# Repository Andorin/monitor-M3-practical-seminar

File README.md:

monitor-M3-practical-seminar
============================

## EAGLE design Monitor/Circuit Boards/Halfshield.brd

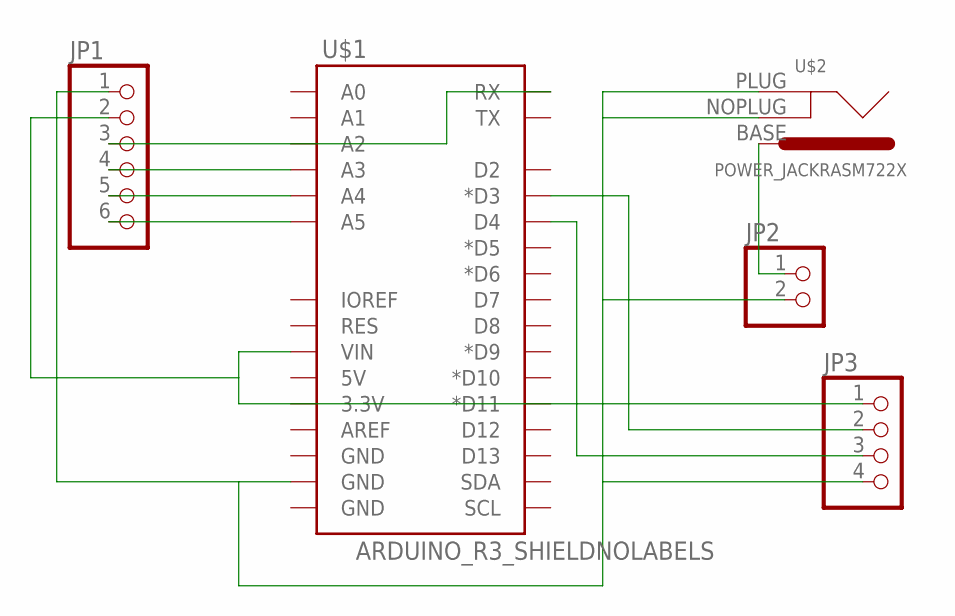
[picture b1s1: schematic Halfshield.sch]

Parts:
JP1: PINHD-1X6; 1X06
JP2: PINHD-1X2; 1X02
JP3: PINHD-1X4; 1X04
U$1: ARDUINO_R3_SHIELDNOLABELS; UNO_R3_SHIELD_NOLABELS
U$2: POWER_JACKRASM722X; RASM722X

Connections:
unnamed: JP1.6, U$1.A5
unnamed: JP1.5, U$1.A4
unnamed: JP1.4, U$1.A3
unnamed: JP1.3, U$1.RX
unnamed: JP1.2, JP3.1, U$1.VIN
unnamed: JP2.1, U$2.BASE (GND)
unnamed: JP1.1, JP2.2, JP3.4, U$1.GND@1 (GND), U$2.NOPLUG (OFF), U$2.PLUG (ON)
unnamed: JP3.3, U$1.D4
unnamed: JP3.2, U$1.D3 (*D3)

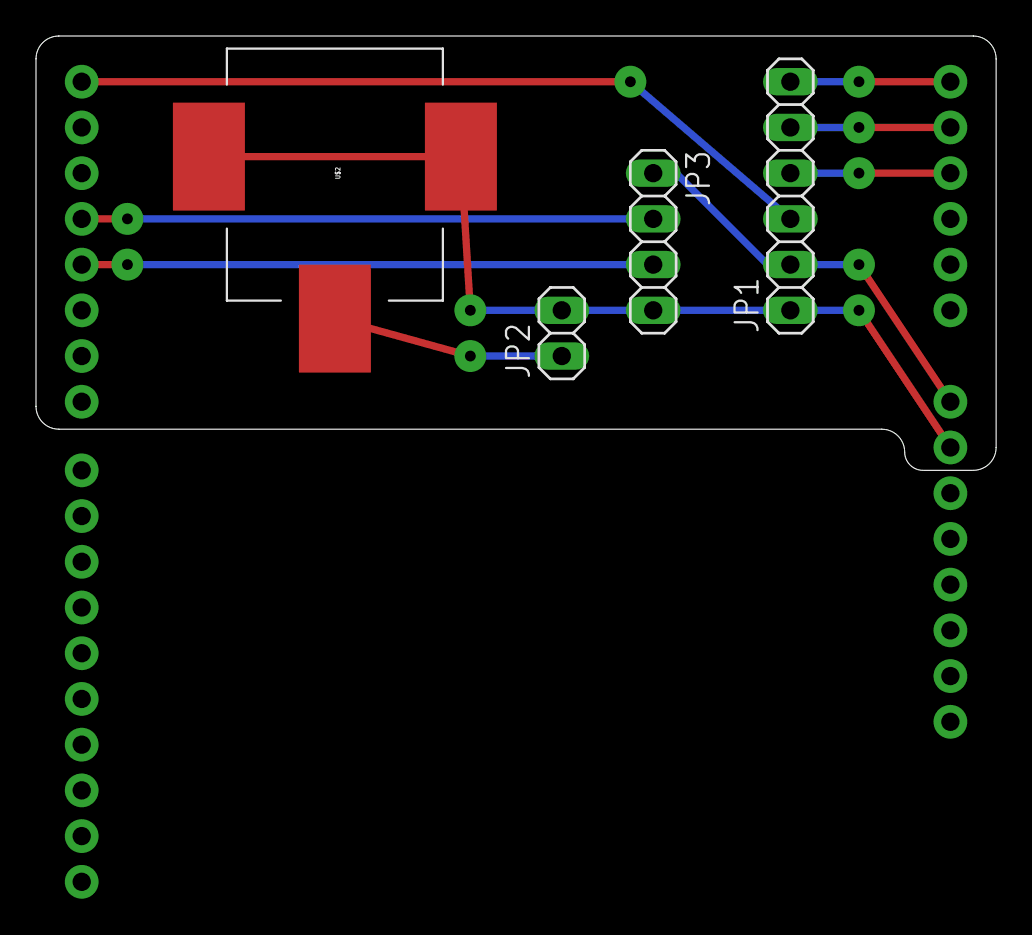
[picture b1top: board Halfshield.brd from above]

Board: 2 copper layers, 53.3 x 24.1 mm, 5 parts (0 on the bottom side), 9 nets.

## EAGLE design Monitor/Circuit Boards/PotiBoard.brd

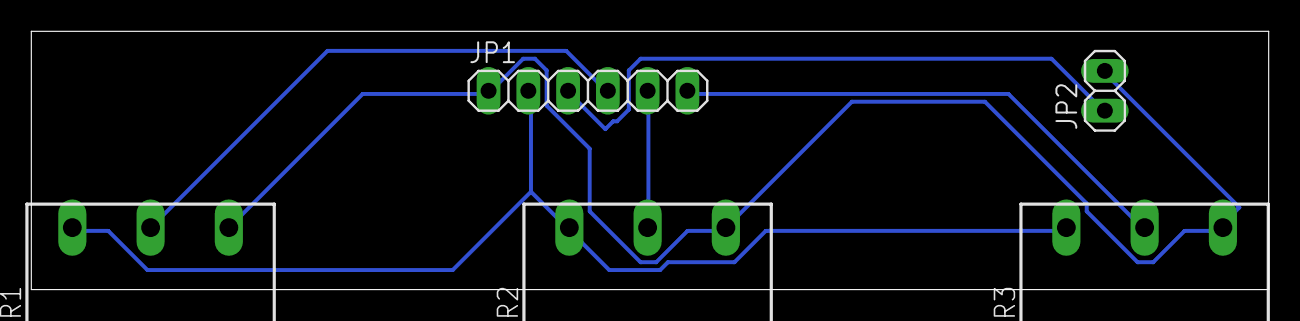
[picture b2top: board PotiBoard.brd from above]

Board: 2 copper layers, 79.0 x 16.5 mm, 5 parts (0 on the bottom side), 6 nets.

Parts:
JP1: 1X06
JP2: 1X02
R1, R2, R3: PC16S

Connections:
unnamed: JP1.2, R1.1A, R2.1A, R3.1A
unnamed: JP1.1, JP2.2, R1.1E, R2.1E, R3.1E
unnamed: JP1.4, R1.1S
unnamed: JP1.5, R2.1S
unnamed: JP1.6, R3.1S
unnamed: JP1.3, JP2.1

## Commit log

2014-07-29 fertig

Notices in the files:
parts and their libraries:
SparkFun-Boards: Licensing: Creative Commons ShareAlike 4.0 International - https://creativecommons.org/licenses/by-sa/4.0
